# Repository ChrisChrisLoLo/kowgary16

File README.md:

# kowgary16

A low profile, ultra-portable companion piece to the bancouver40

# Note
This keypad works 17x17 choc keycaps, like the Chosfox CFX keycaps. This will _not_ fit with MBK or kailh choc keycaps.

# Status
This macropad is confirmed to work!

# BOM
BOM for pcb included in the `pcb` folder. You will additionally need 4 rubber feet, the aluminum CNC case, as well as 4x 4mm M2 screws

# Acknowledgements
Thank you [PCBWay](https://www.pcbway.com/) for sponsoring this project! It continues to impress me that I can use their services to make consumer grade enclosures. I've been going with their bead blasted anodized aluminum offerings with the premium finish option selected, and am continually thrilled by the quality. I only had to pay $48 USD to get the kowgary case manufactured, which is a fantastic price for a premium feeling macropad!

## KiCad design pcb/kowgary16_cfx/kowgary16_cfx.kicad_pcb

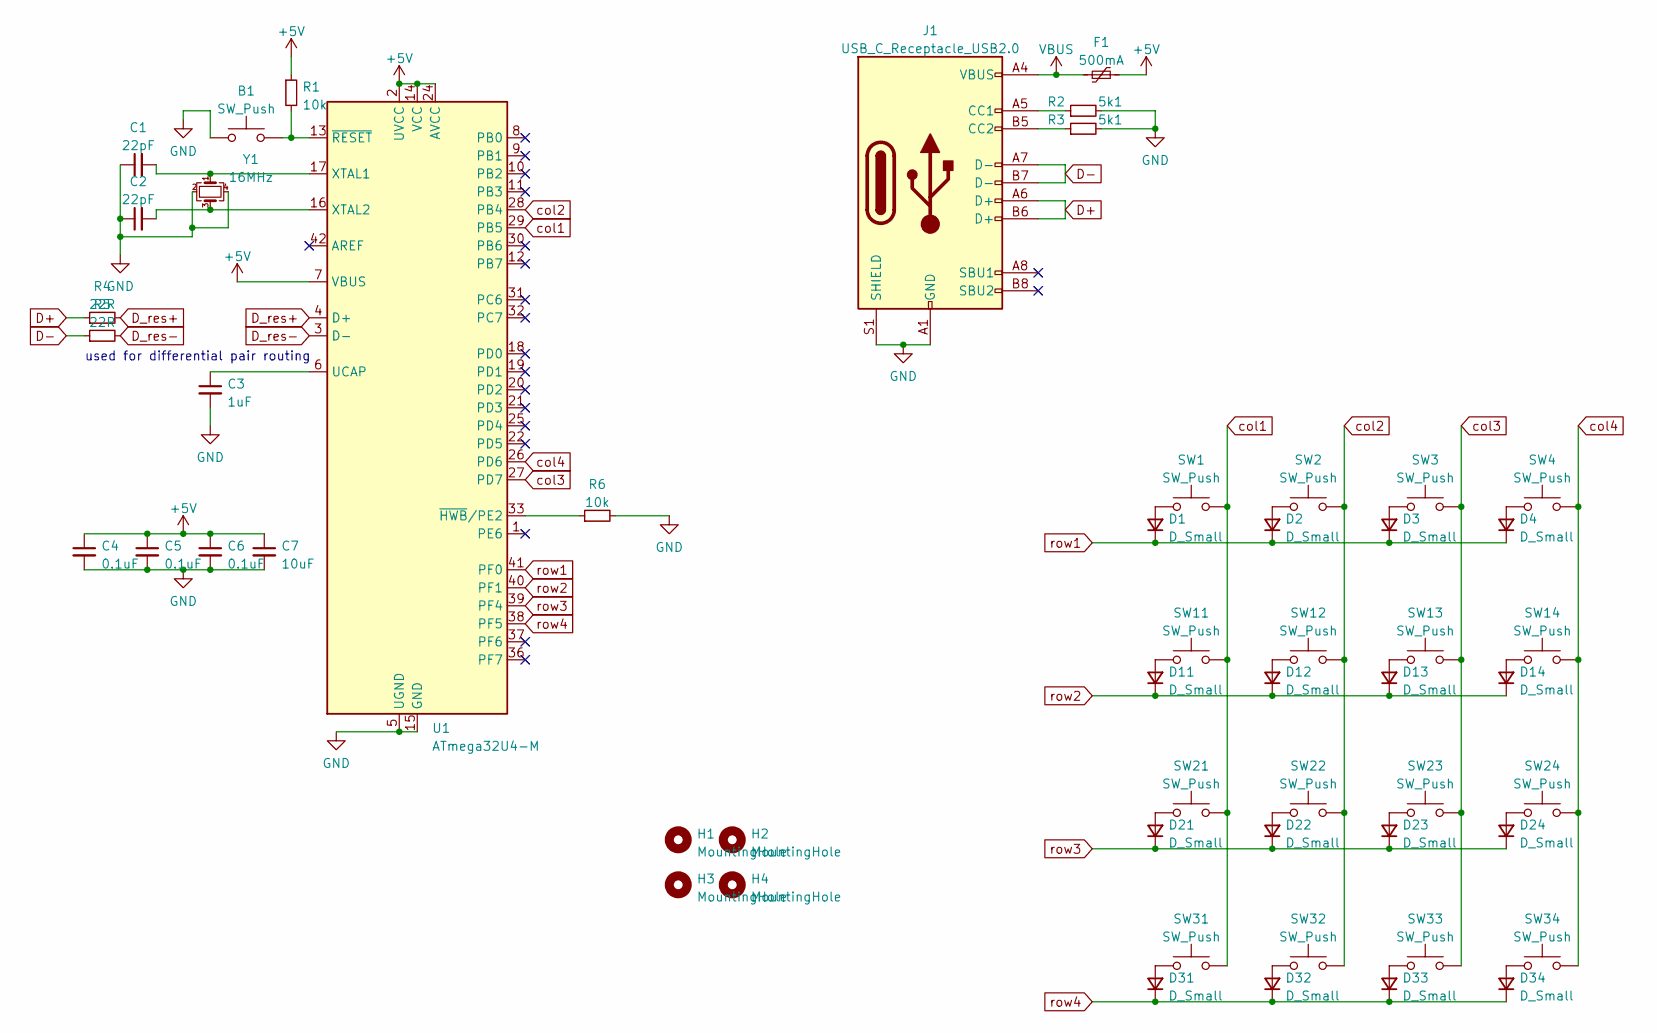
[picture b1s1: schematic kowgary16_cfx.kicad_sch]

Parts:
B1: SW_Push; SW_SPST_SKQG_WithoutStem
C1, C2: 22pF; C_0402_1005Metric
C3: 1uF; C_0402_1005Metric
C4, C5, C6: 0.1uF; C_0402_1005Metric
C7: 10uF; C_0402_1005Metric
D1, D2, D3, D4, D11, D12, D13, D14, D21, D22, D23, D24, D31, D32, D33, D34: D_Small; D_SOD-323
F1: 500mA; Fuse_1206_3216Metric
H1, H2, H3, H4: MountingHole; MountingHole_2.2mm_M2_ISO7380
J1: USB_C_Receptacle_USB2.0; USB_C_Receptacle_XKB_U262-16XN-4BVC11
R1, R6: 10k; R_0402_1005Metric
R2, R3: 5k1; R_0402_1005Metric
R4, R5: 22R; R_0402_1005Metric
SW1, SW2, SW3, SW4, SW11, SW12, SW13, SW14, SW21, SW22, SW23, SW24, SW31, SW32, SW33, SW34: SW_Push; Kailh_socket_PG1350
U1: ATmega32U4-M; QFN-44-1EP_7x7mm_P0.5mm_EP5.2x5.2mm
Y1: 16MHz; Crystal_SMD_3225-4Pin_3.2x2.5mm

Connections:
+5V: C4.1, C5.1, C6.1, C7.1, F1.2, R1.1, U1.2 (UVCC), U1.7 (VBUS), U1.14 (VCC), U1.24 (AVCC), U1.34 (VCC), U1.44 (AVCC)
D+: J1.A6 (D+), J1.B6 (D+), R4.1
D-: J1.A7 (D-), J1.B7 (D-), R5.1
D_res+: R4.2, U1.4 (D+)
D_res-: R5.2, U1.3 (D-)
GND: B1.1, C1.1, C2.1, C3.2, C4.2, C5.2, C6.2, C7.2, J1.A1 (GND), J1.A12 (GND), J1.B1 (GND), J1.B12 (GND), J1.S1 (SHIELD), R2.2, R3.2, R6.2, U1.5 (UGND), U1.15 (GND), U1.23 (GND), U1.35 (GND), U1.43 (GND), U1.45 (GND), Y1.2, Y1.4
unnamed: B1.2, R1.2, U1.13 (~RESET)
unnamed: C1.2, U1.17 (XTAL1), Y1.1
unnamed: C2.2, U1.16 (XTAL2), Y1.3
unnamed: C3.1, U1.6 (UCAP)
unnamed: D1.2 (A), SW1.1
unnamed: D2.2 (A), SW2.1
unnamed: D3.2 (A), SW3.1
unnamed: D4.2 (A), SW4.1
unnamed: D11.2 (A), SW11.1
unnamed: D12.2 (A), SW12.1
unnamed: D13.2 (A), SW13.1
unnamed: D14.2 (A), SW14.1
unnamed: D21.2 (A), SW21.1
unnamed: D22.2 (A), SW22.1
unnamed: D23.2 (A), SW23.1
unnamed: D24.2 (A), SW24.1
unnamed: D31.2 (A), SW31.1
unnamed: D32.2 (A), SW32.1
unnamed: D33.2 (A), SW33.1
unnamed: D34.2 (A), SW34.1
unnamed: J1.A5 (CC1), R2.1
unnamed: J1.B5 (CC2), R3.1
unnamed: R6.1, U1.33 (~HWB/PE2)
VBUS: F1.1, J1.A4 (VBUS), J1.A9 (VBUS), J1.B4 (VBUS), J1.B9 (VBUS)
col1: SW1.2, SW11.2, SW21.2, SW31.2, U1.29 (PB5)
col2: SW2.2, SW12.2, SW22.2, SW32.2, U1.28 (PB4)
col3: SW3.2, SW13.2, SW23.2, SW33.2, U1.27 (PD7)
col4: SW4.2, SW14.2, SW24.2, SW34.2, U1.26 (PD6)
row1: D1.1 (K), D2.1 (K), D3.1 (K), D4.1 (K), U1.41 (PF0)
row2: D11.1 (K), D12.1 (K), D13.1 (K), D14.1 (K), U1.40 (PF1)
row3: D21.1 (K), D22.1 (K), D23.1 (K), D24.1 (K), U1.39 (PF4)
row4: D31.1 (K), D32.1 (K), D33.1 (K), D34.1 (K), U1.38 (PF5)

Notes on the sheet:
used for differential pair routing

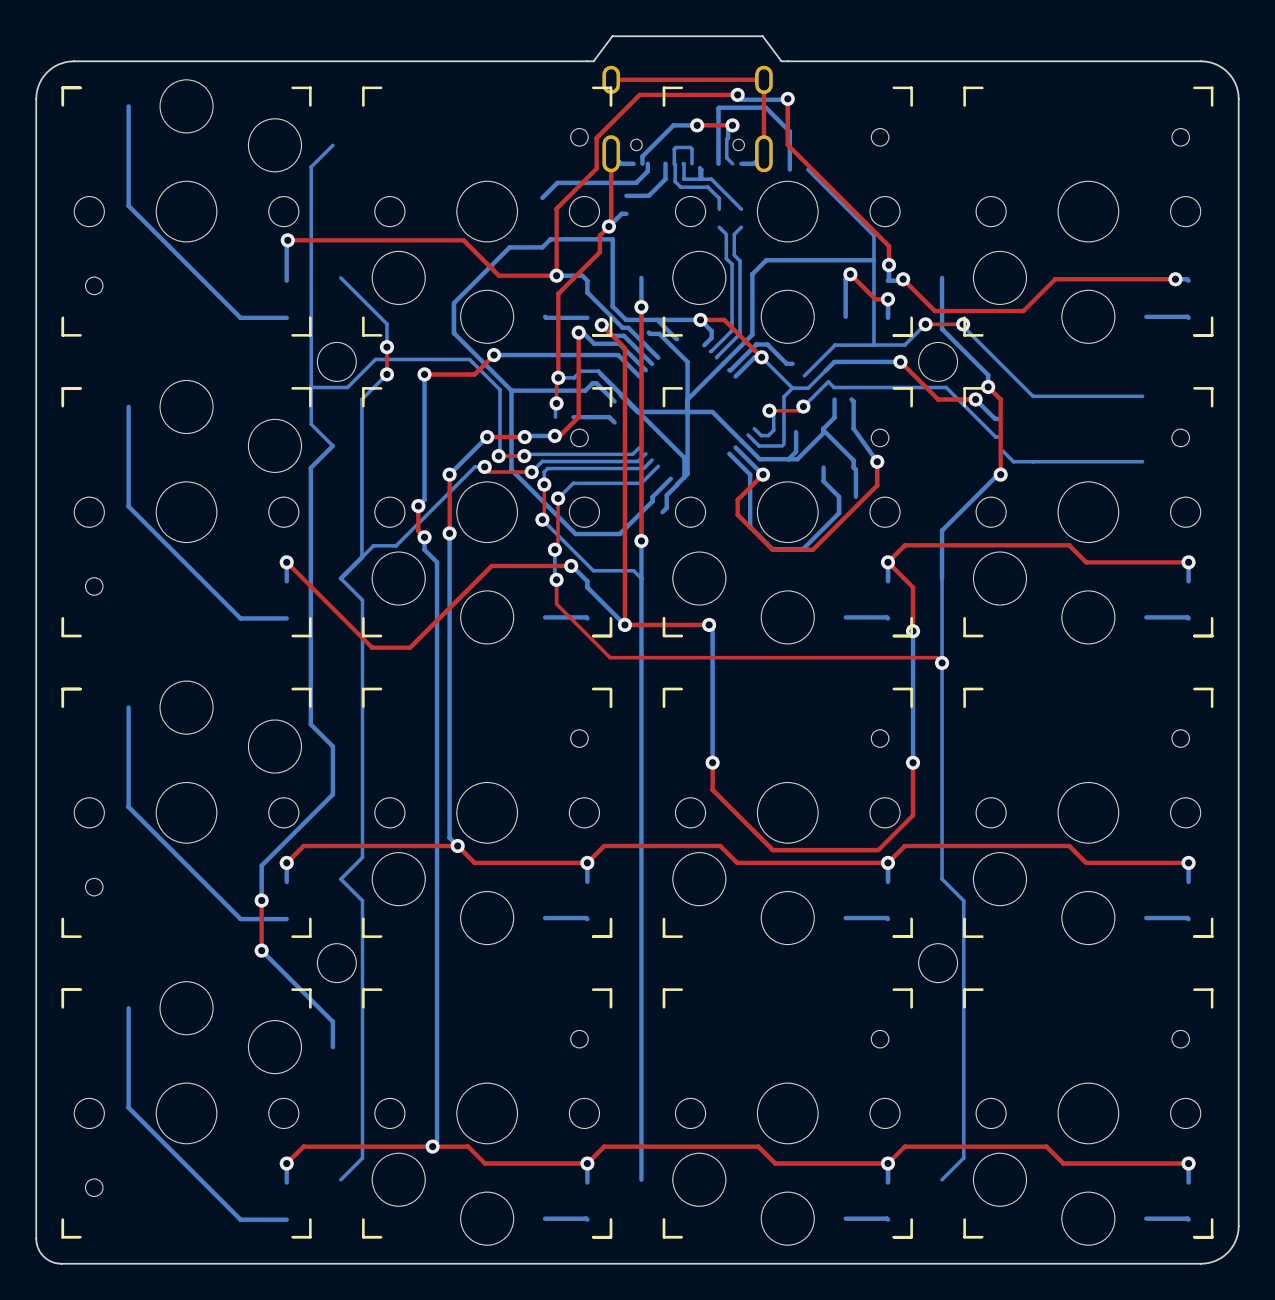
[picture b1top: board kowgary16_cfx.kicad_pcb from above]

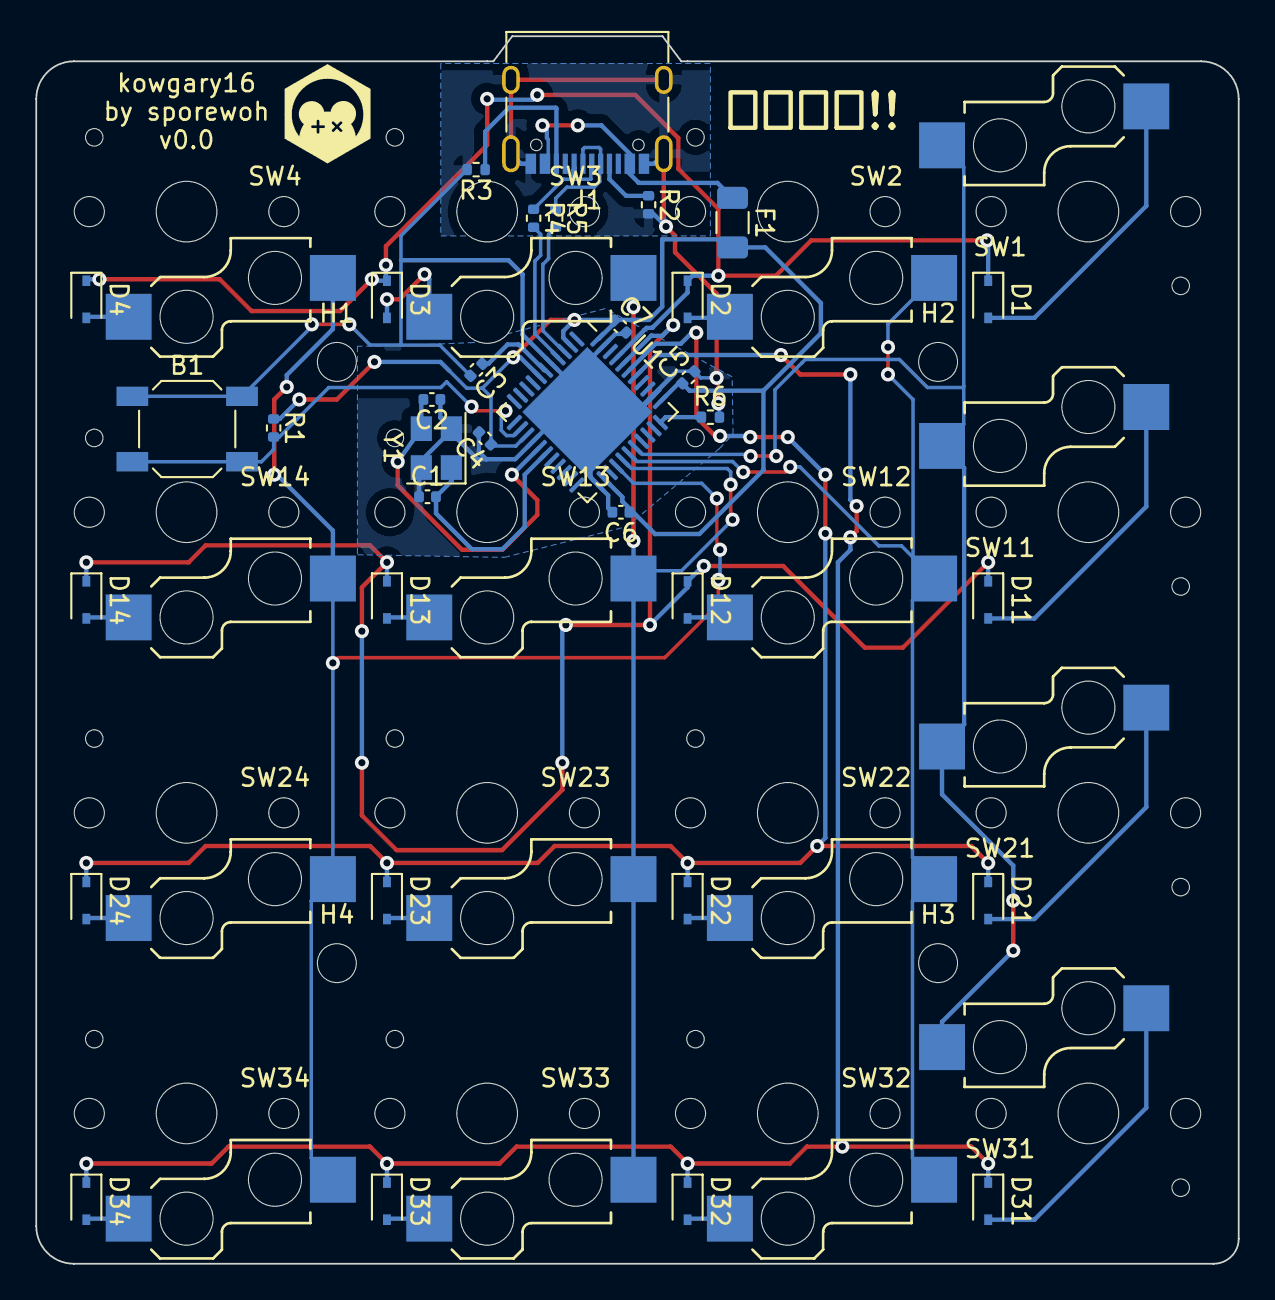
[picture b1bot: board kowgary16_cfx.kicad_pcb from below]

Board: 2 copper layers, 68.0 x 69.4 mm, 54 parts (38 on the bottom side), 38 nets.

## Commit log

2023-01-21 init commit
